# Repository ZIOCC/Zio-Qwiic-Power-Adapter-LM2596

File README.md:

# Zio Qwiic Power Adapter

> ###### About Zio
> Zio is a new line of open sourced, compact, and grid layout boards, fully integrated for Arduino and Qwiic ecosystem. Designed ideally for wearables, robotics, small-space limitations or other on the go projects. Check out other awesome Zio products [here](https://www.smart-prototyping.com/Zio)

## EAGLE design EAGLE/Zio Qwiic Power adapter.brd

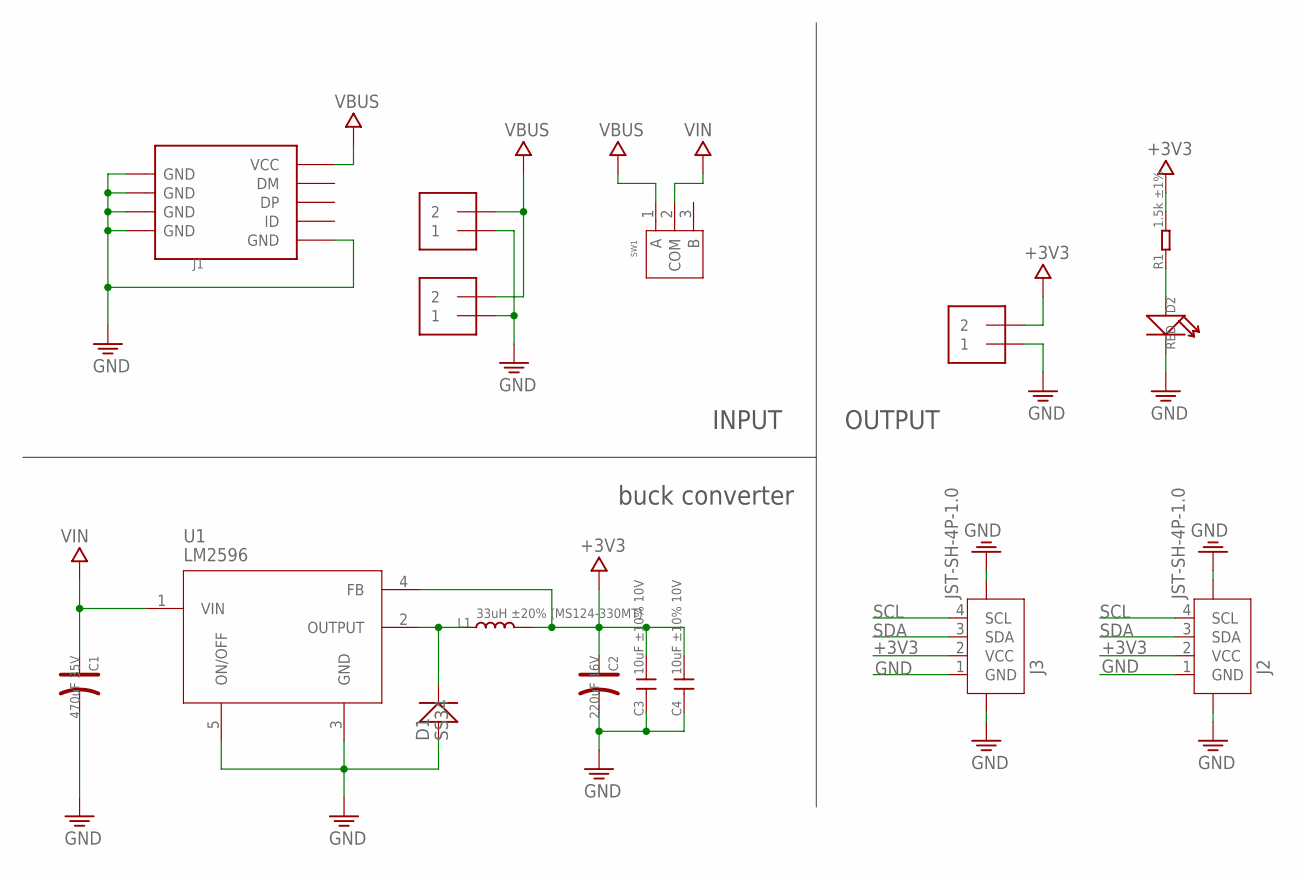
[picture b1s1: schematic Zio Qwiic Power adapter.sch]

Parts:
C1: 470uF 35V; ELECTRO-SMD-G-10MM
C2: 220uF 16V; ELECTRO-SMD-C-6MM
C3, C4: 10uF ±10% 10V; C1206
D1: SS34; SMA
D2: RED; LED-0603
J1: USB-MICROE; MICRO-SMD
J2, J3: JST-SH-4P-1.0; JST-SH-4P
J4, J5, J6: TERMBLOCK_1X2-3.5MM; 1X2-3.5MM
L1: 33uH ±20% (MS124-330MT); L-12.2*12.2
R1: 1.5k ±1%; R0603
SW1: SWITCH-2H-3P2A/3A; 3P-2CH-12.7X6.6X6.35H
U1: LM2596; TO-263

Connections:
+3V3: C2.+, C3.2, C4.2, J2.2 (VCC), J3.2 (VCC), J5.2, L1.2, R1.2, U1.4 (FB)
GND: C1.-, C2.-, C3.1, C4.1, D1.P$2 (+), D2.-, J1.GND, J1.S1 (GND), J1.S1@1 (GND), J1.S1@2 (GND), J1.S2 (GND), J1.S2@1 (GND), J1.S2@2 (GND), J1.S3 (GND), J1.S3@1 (GND), J1.S3@2 (GND), J1.S4 (GND), J1.S4@1 (GND), J1.S4@2 (GND), J1.S5 (GND), J1.S6 (GND), J2.1 (GND), J2.NC1 (5), J2.NC2 (6), J3.1 (GND), J3.NC1 (5), J3.NC2 (6), J4.1, J5.1, J6.1, U1.3 (GND), U1.5 (ON/OFF)
unnamed: D2.+, R1.1
OUTPUT: D1.P$1 (-), L1.1, U1.2 (OUTPUT)
SCL: J2.4 (SCL), J3.4 (SCL)
SDA: J2.3 (SDA), J3.3 (SDA)
VBUS: J1.VBUS (VCC), J4.2, J6.2, SW1.1 (A)
VIN: C1.+, SW1.2 (COM), U1.1 (VIN)

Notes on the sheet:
INPUT
buck converter
OUTPUT

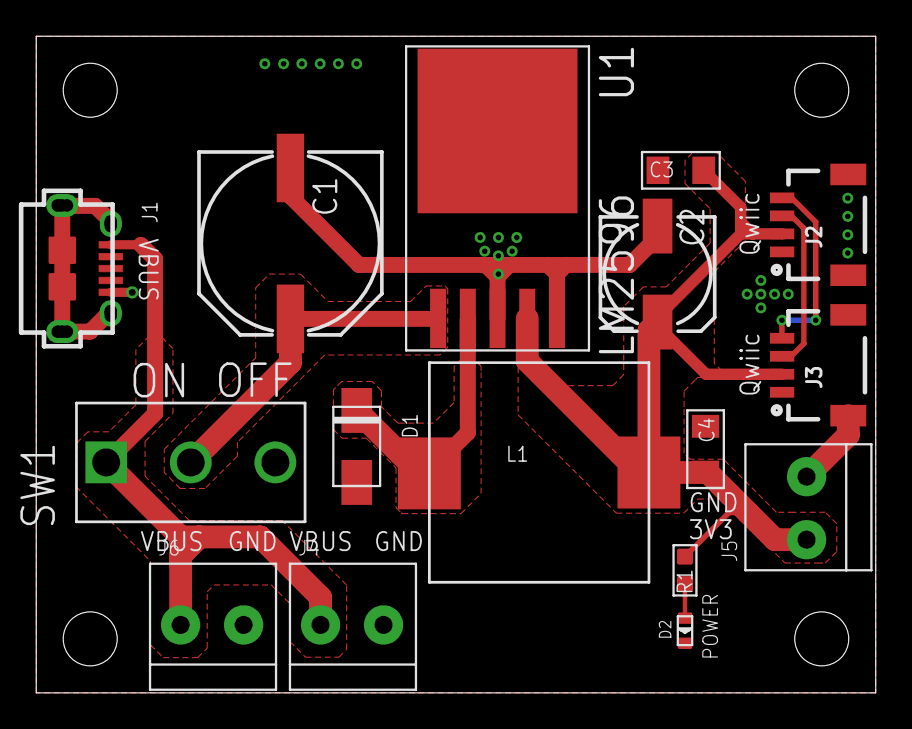
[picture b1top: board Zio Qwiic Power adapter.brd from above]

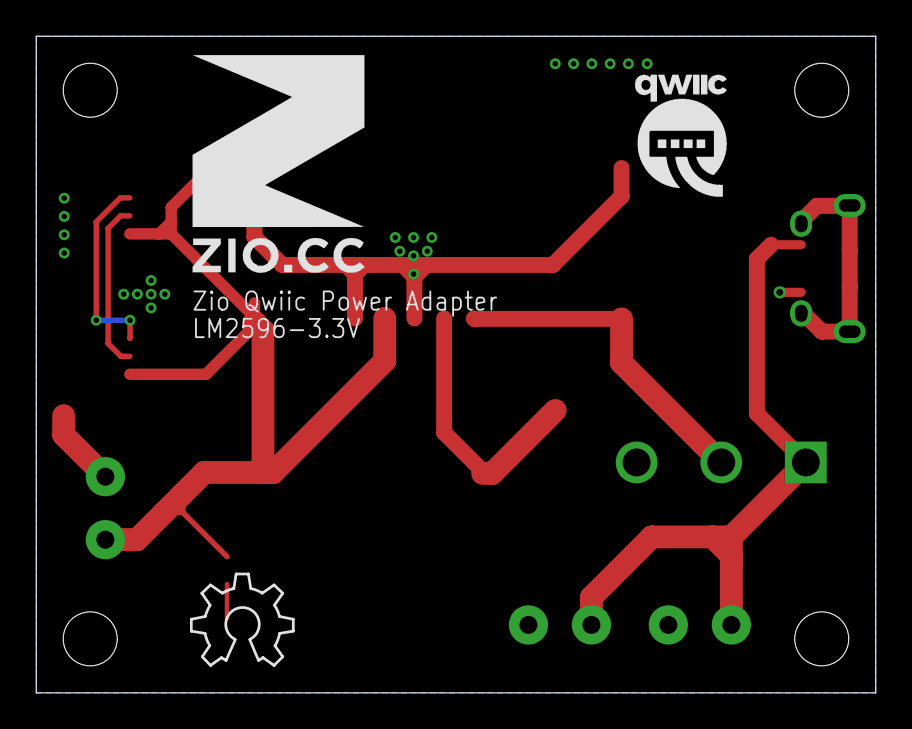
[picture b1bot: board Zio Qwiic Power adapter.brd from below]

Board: 2 copper layers, 46.6 x 36.5 mm, 19 parts (3 on the bottom side), 8 nets.

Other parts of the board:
U$6: 12MM
U$7: QWIIC-LOGO-MEDIUM
U$8: OSHW_6X200_NOTEXT

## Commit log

2019-05-31 Upload source files
    Uploaded PCB Source files: Schematics, EAGLE, gerber and datatsheet
